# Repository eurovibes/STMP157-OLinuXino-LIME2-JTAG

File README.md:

<!-- SPDX-FileCopyrightText: 2022 Benedikt Spranger <b.spranger@linutronix.de> -->
<!-- SPDX-License-Identifier: CERN-OHL-S-2.0 -->

# STMP157-OLinuXino-LIME2-JTAG - Olimex STMP157-OLinuXino-LIME2 JTAG breakout board

On the Olimex [STMP157-OLinuXino-LIME2 board](https://www.olimex.com/Products/OLinuXino/STMP1/open-source-hardware)
the JTAG signals are routed to GPIO 3 and not to a common JTAG connector.
STMP157-OLinuXino-LIME2-JTAG is a breakout board to connect common JTAG
adapters to the board.

## License rules

STMP157-OLinuXino-LIME2-JTAG is provided under the terms of the CERN-OHL-S
license version 2 as provided in the LICENSES/CERN-OHL-S-2.0 file.

Instead of adding license boilerplates to the individual files,
STMP157-OLinuXino-LIME2-JTAG uses SPDX license identifiers, which are machine
parseable and considered legaly equivalent.

The SPDX license identifier in STMP157-OLinuXino-LIME2-JTAG shall be added at
the first possible line in a file which can contain a comment. This is
normally the first line except for scripts. Scripts require the
#!PATH_TO_INTERPRETER tag in the first line; place the SPDX identifier into
the second line.

The SPDX license identifier is added in form of a comment.

## Copyright and License

>Copyright Benedikt Spranger 2021.
>This source describes Open Hardware and is licensed under the CERNOHL-S v2.
>You may redistribute and modify this source and make products using it
>under the terms of the CERN-OHL-S v2
>(https://ohwr.org/cern ohl s v2.txt ).
>This source is distributed WITHOUT ANY EXPRESS OR IMPLIED
>WARRANTY, INCLUDING OF MERCHANTABILITY, SATISFACTORY
>QUALITY AND FITNESS FOR A PARTICULAR PURPOSE. Please see
>the CERN-OHL-S v2 for applicable conditions.
>Source location: https://github.com/eurovibes/STMP157-OLinuXino-LIME2-JTAG
>As per CERN-OHL-S v2 section 4, should You produce hardware based
>on this source, You must where practicable maintain the Source Location
>visible on the external case of the STMP157-OLinuXino-LIME2-JTAG or other
>products you make using this source.

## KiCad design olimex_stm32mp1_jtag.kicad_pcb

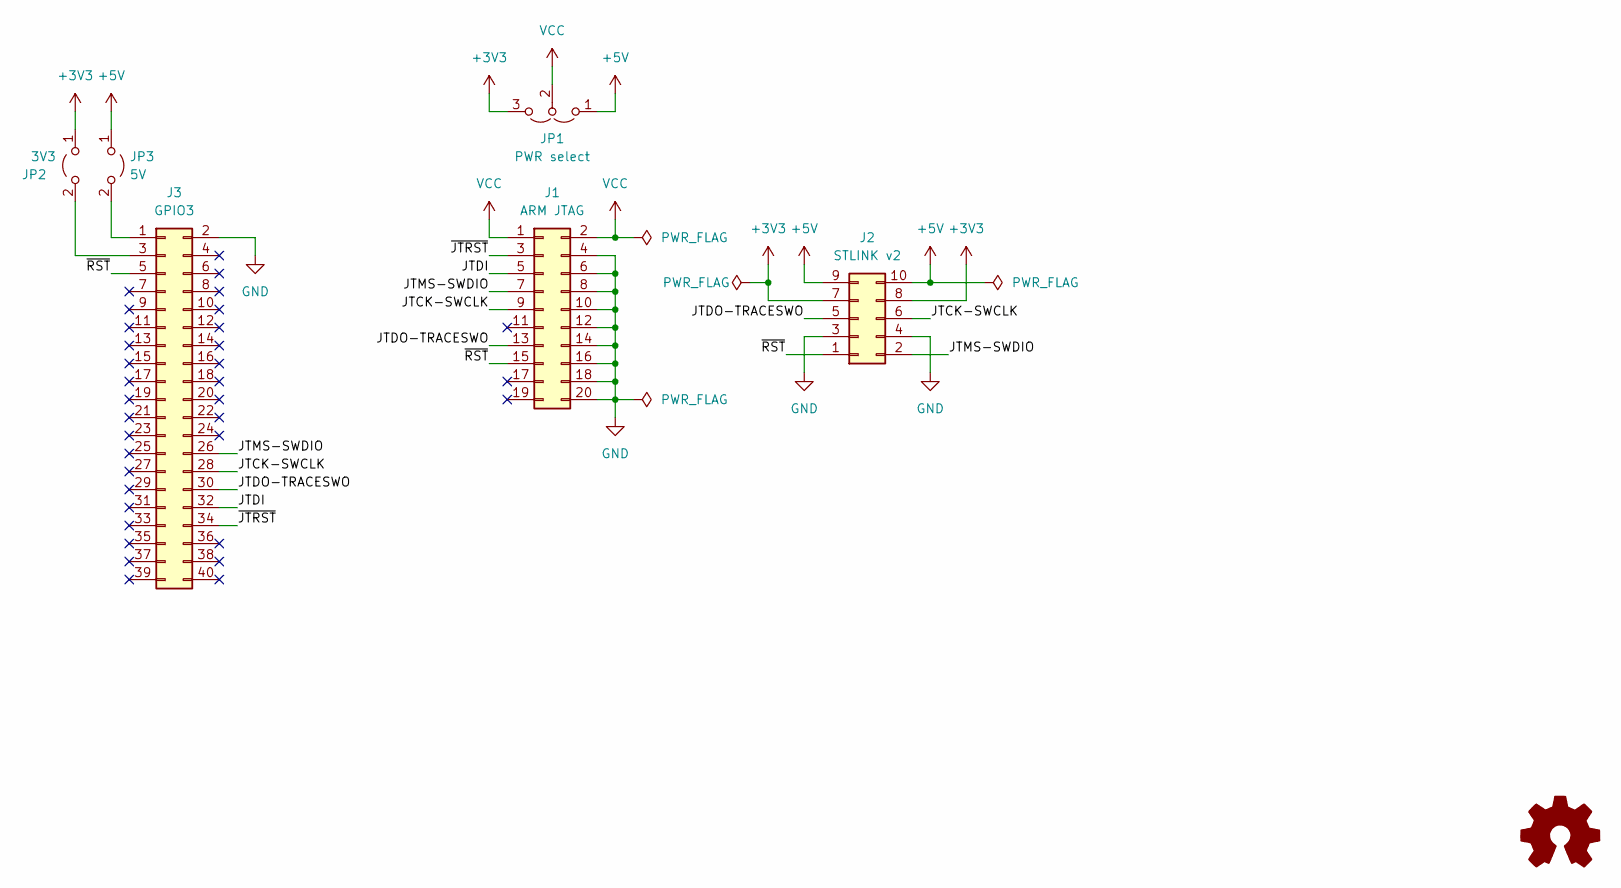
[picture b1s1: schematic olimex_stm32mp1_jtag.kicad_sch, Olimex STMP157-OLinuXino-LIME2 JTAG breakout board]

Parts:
J1: ARM JTAG; PinHeader_2x10_P2.54mm_Vertical
J2: STLINK v2; PinHeader_2x05_P2.54mm_Vertical
J3: GPIO3; PinSocket_2x20_P1.27mm_Vertical
JP1: PWR select; PinHeader_1x03_P2.54mm_Vertical
JP2: 3V3; PinHeader_1x02_P2.54mm_Vertical
JP3: 5V; PinHeader_1x02_P2.54mm_Vertical

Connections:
+3V3: J2.7, J2.8, JP1.3 (B), JP2.1 (A)
+5V: J2.9, J2.10, JP1.1 (A), JP3.1 (A)
/JTCK-SWCLK: J1.9, J2.6, J3.28
/JTDI: J1.5, J3.32
/JTDO-TRACESWO: J1.13, J2.5, J3.30
/JTMS-SWDIO: J1.7, J2.2, J3.26
/~JTRST: J1.3, J3.34
/~RST: J1.15, J2.1, J3.5
GND: J1.4, J1.6, J1.8, J1.10, J1.12, J1.14, J1.16, J1.18, J1.20, J2.3, J2.4, J3.2
unnamed: J3.1, JP3.2 (B)
unnamed: J3.3, JP2.2 (B)
VCC: J1.1, J1.2, JP1.2 (C)

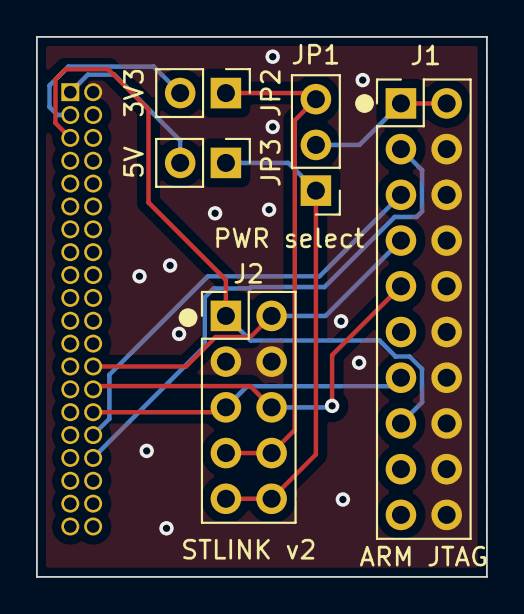
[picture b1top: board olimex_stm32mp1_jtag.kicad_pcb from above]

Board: 2 copper layers, 25.0 x 30.0 mm, 6 parts (1 on the bottom side), 12 nets.

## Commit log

2022-08-16 Initial
2022-08-16 Deploying to gh-pages from @ eurovibes/STMP157-OLinuXino-LIME2-JTAG@be40aa72f8345a46599b581aa04471cad227102a 🚀
2022-08-16 Initial gh-pages commit

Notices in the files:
olimex_stm32mp1_jtag.kicad_sch:
This work is licensed under the CERN-OHL-S v2
